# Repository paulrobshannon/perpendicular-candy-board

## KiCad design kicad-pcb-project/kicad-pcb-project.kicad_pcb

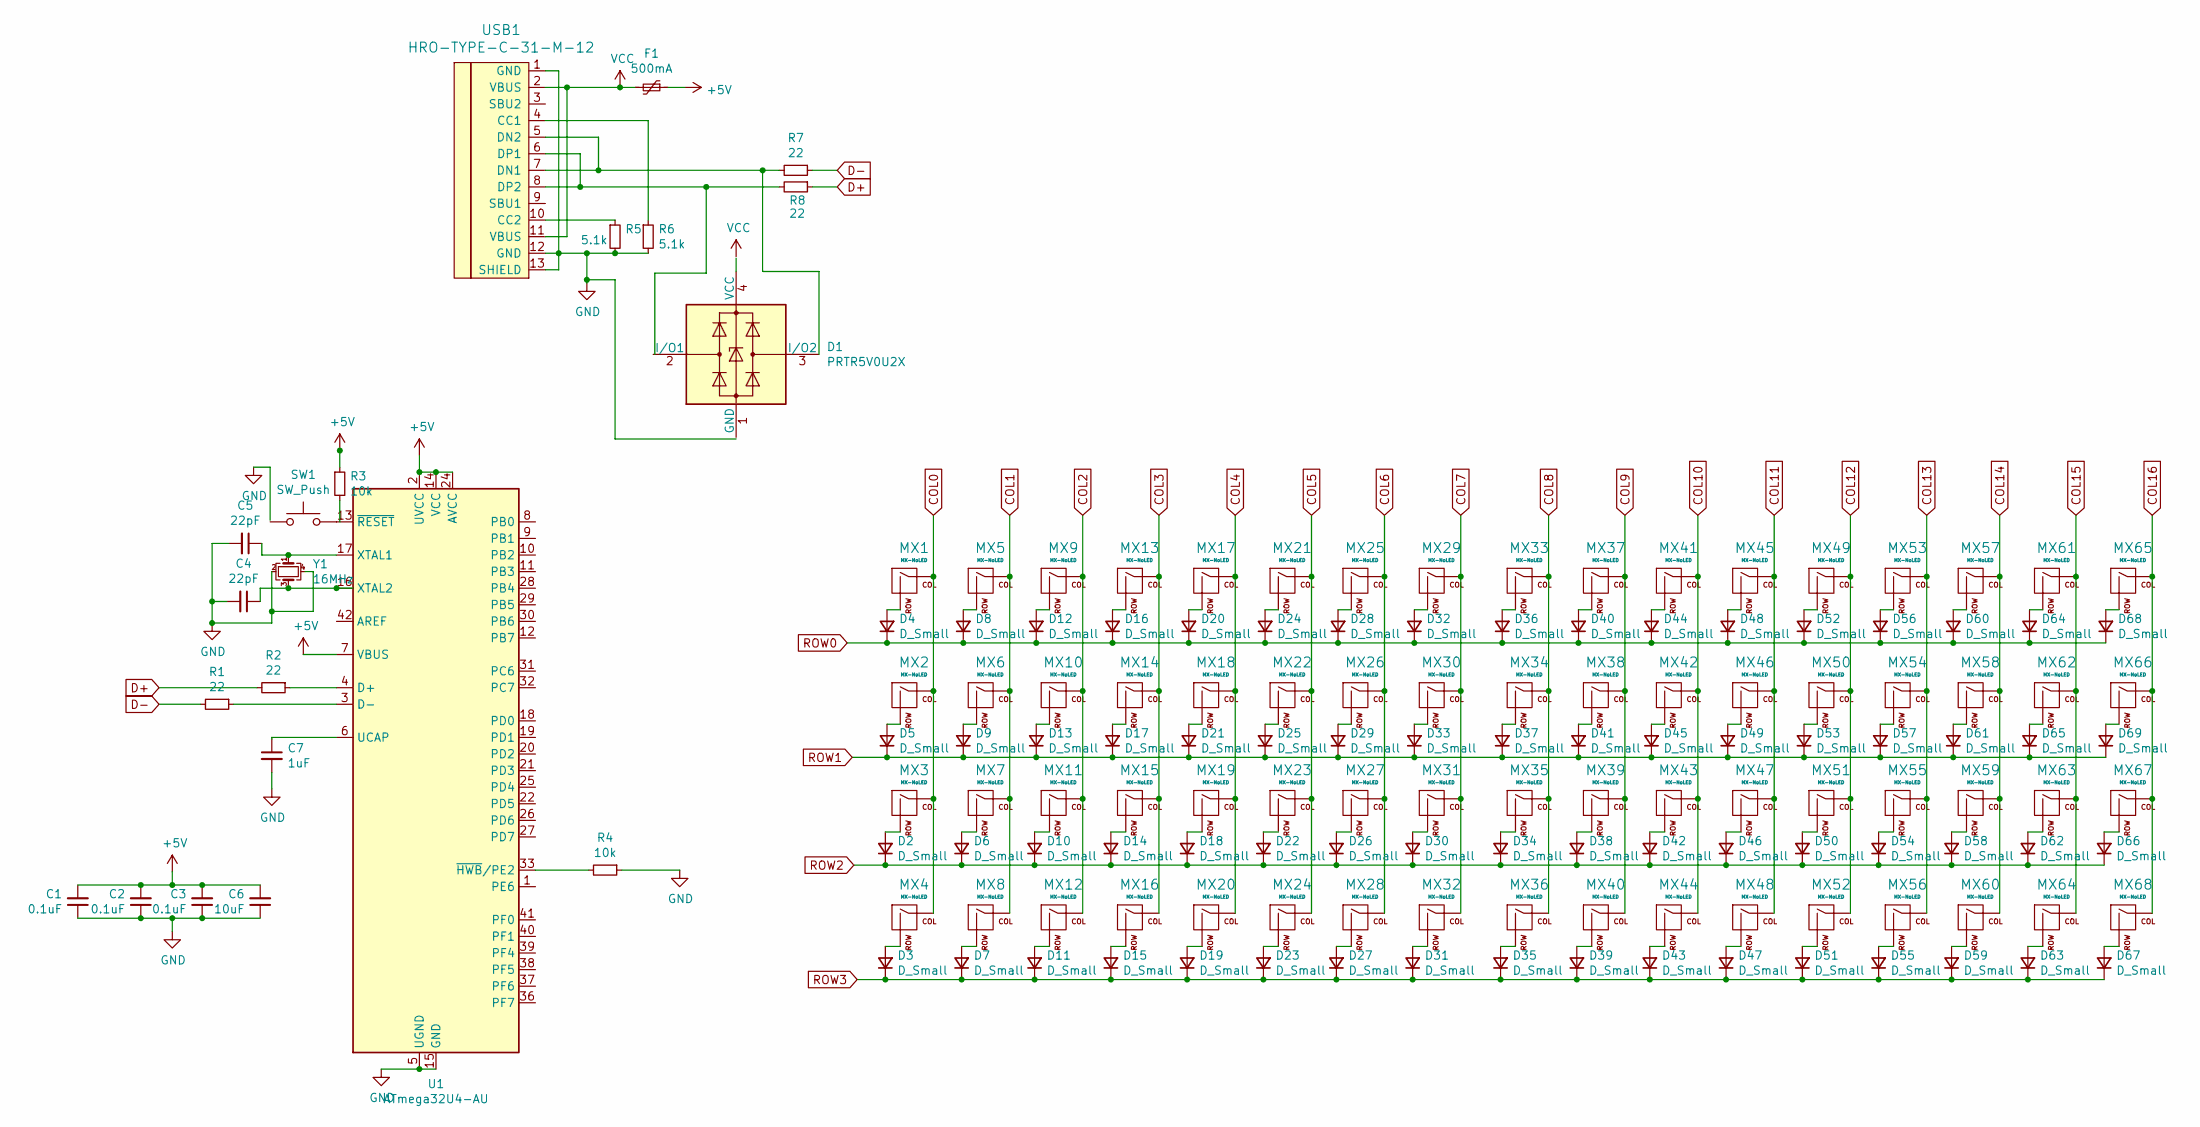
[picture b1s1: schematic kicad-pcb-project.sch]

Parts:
C1, C2, C3: 0.1uF; C_0805_2012Metric
C4, C5: 22pF; C_0805_2012Metric
C6: 10uF; C_0805_2012Metric
C7: 1uF; D_SOD-123
D1: PRTR5V0U2X; D_SOD-123
D2, D3, D4, D5, D6, D7, D8, D9, D10, D11, D12, D13, D14, D15, D16, D17, D18, D19, D20, D21, D22, D23, D24, D25, D26, D27, D28, D29, D30, D31, D32, D33, D34, D35, D36, D37, D38, D39, D40, D41, D42, D43, D44, D45, D46, D47, D48, D49, D50, D51, D52, D53, D54, D55, D56, D57, D58, D59, D60, D61, D62, D63, D64, D65, D66, D67, D68, D69: D_Small; D_SOD-123
F1: 500mA; Fuse_1206_3216Metric
MX1, MX2, MX3, MX4, MX5, MX6, MX7, MX8, MX9, MX10, MX11, MX12, MX13, MX14, MX15, MX16, MX17, MX18, MX19, MX20, MX21, MX22, MX23, MX24, MX25, MX26, MX27, MX28, MX29, MX30, MX31, MX32, MX33, MX34, MX35, MX36, MX37, MX38, MX39, MX40, MX41, MX42, MX43, MX44, MX45, MX46, MX47, MX48, MX49, MX50, MX51, MX52, MX53, MX54, MX55, MX56, MX57, MX58, MX59, MX60, MX61, MX62, MX63, MX64, MX65, MX66, MX67, MX68: MX-NoLED; Kailh_socket_MX
R1, R2, R7, R8: 22; R_0805_2012Metric
R3, R4: 10k; R_0805_2012Metric
R5, R6: 5.1k; R_0805_2012Metric
SW1: SW_Push; SKQG-1155865
U1: ATmega32U4-AU; TQFP-44_10x10mm_P0.8mm
USB1: HRO-TYPE-C-31-M-12; HRO-TYPE-C-31-M-12-Assembly
Y1: 16MHz; Crystal_SMD_3225-4Pin_3.2x2.5mm

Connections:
+5V: C1.2, C2.2, C3.2, C6.2, F1.1, R3.1, U1.2 (UVCC), U1.7 (VBUS), U1.14 (VCC), U1.24 (AVCC), U1.34 (VCC), U1.44 (AVCC)
COL0: MX1.1 (COL), MX2.1 (COL), MX3.1 (COL), MX4.1 (COL)
COL1: MX5.1 (COL), MX6.1 (COL), MX7.1 (COL), MX8.1 (COL)
COL2: MX9.1 (COL), MX10.1 (COL), MX11.1 (COL), MX12.1 (COL)
COL3: MX13.1 (COL), MX14.1 (COL), MX15.1 (COL), MX16.1 (COL)
COL4: MX17.1 (COL), MX18.1 (COL), MX19.1 (COL), MX20.1 (COL)
COL5: MX21.1 (COL), MX22.1 (COL), MX23.1 (COL), MX24.1 (COL)
COL6: MX25.1 (COL), MX26.1 (COL), MX27.1 (COL), MX28.1 (COL)
COL7: MX29.1 (COL), MX30.1 (COL), MX31.1 (COL), MX32.1 (COL)
COL8: MX33.1 (COL), MX34.1 (COL), MX35.1 (COL), MX36.1 (COL)
COL9: MX37.1 (COL), MX38.1 (COL), MX39.1 (COL), MX40.1 (COL)
COL10: MX41.1 (COL), MX42.1 (COL), MX43.1 (COL), MX44.1 (COL)
COL11: MX45.1 (COL), MX46.1 (COL), MX47.1 (COL), MX48.1 (COL)
COL12: MX49.1 (COL), MX50.1 (COL), MX51.1 (COL), MX52.1 (COL)
COL13: MX53.1 (COL), MX54.1 (COL), MX55.1 (COL), MX56.1 (COL)
COL14: MX57.1 (COL), MX58.1 (COL), MX59.1 (COL), MX60.1 (COL)
COL15: MX61.1 (COL), MX62.1 (COL), MX63.1 (COL), MX64.1 (COL)
COL16: MX65.1 (COL), MX66.1 (COL), MX67.1 (COL), MX68.1 (COL)
D+: R2.2, R8.1
D-: R1.2, R7.1
GND: C1.1, C2.1, C3.1, C4.2, C5.2, C6.1, C7.2, R4.1, R5.2, R6.2, U1.5 (UGND), U1.15 (GND), U1.23 (GND), U1.35 (GND), U1.43 (GND), USB1.1 (GND), USB1.12 (GND), USB1.13 (SHIELD), Y1.2, Y1.4
unnamed: C4.1, U1.16 (XTAL2), Y1.3
unnamed: C5.1, U1.17 (XTAL1), Y1.1
unnamed: C7.1, U1.6 (UCAP)
unnamed: D1.3 (I/O2), R7.2, USB1.5 (DN2), USB1.7 (DN1)
unnamed: D2.2 (A), MX3.2 (ROW)
unnamed: D3.2 (A), MX4.2 (ROW)
unnamed: D4.2 (A), MX1.2 (ROW)
unnamed: D5.2 (A), MX2.2 (ROW)
unnamed: D6.2 (A), MX7.2 (ROW)
unnamed: D7.2 (A), MX8.2 (ROW)
unnamed: D8.2 (A), MX5.2 (ROW)
unnamed: D9.2 (A), MX6.2 (ROW)
unnamed: D10.2 (A), MX11.2 (ROW)
unnamed: D11.2 (A), MX12.2 (ROW)
unnamed: D12.2 (A), MX9.2 (ROW)
unnamed: D13.2 (A), MX10.2 (ROW)
unnamed: D14.2 (A), MX15.2 (ROW)
unnamed: D15.2 (A), MX16.2 (ROW)
unnamed: D16.2 (A), MX13.2 (ROW)
unnamed: D17.2 (A), MX14.2 (ROW)
unnamed: D18.2 (A), MX19.2 (ROW)
unnamed: D19.2 (A), MX20.2 (ROW)
unnamed: D20.2 (A), MX17.2 (ROW)
unnamed: D21.2 (A), MX18.2 (ROW)
unnamed: D22.2 (A), MX23.2 (ROW)
unnamed: D23.2 (A), MX24.2 (ROW)
unnamed: D24.2 (A), MX21.2 (ROW)
unnamed: D25.2 (A), MX22.2 (ROW)
unnamed: D26.2 (A), MX27.2 (ROW)
unnamed: D27.2 (A), MX28.2 (ROW)
unnamed: D28.2 (A), MX25.2 (ROW)
unnamed: D29.2 (A), MX26.2 (ROW)
unnamed: D30.2 (A), MX31.2 (ROW)
unnamed: D31.2 (A), MX32.2 (ROW)
unnamed: D32.2 (A), MX29.2 (ROW)
unnamed: D33.2 (A), MX30.2 (ROW)
unnamed: D34.2 (A), MX35.2 (ROW)
unnamed: D35.2 (A), MX36.2 (ROW)
unnamed: D36.2 (A), MX33.2 (ROW)
unnamed: D37.2 (A), MX34.2 (ROW)
unnamed: D38.2 (A), MX39.2 (ROW)
unnamed: D39.2 (A), MX40.2 (ROW)
unnamed: D40.2 (A), MX37.2 (ROW)
unnamed: D41.2 (A), MX38.2 (ROW)
unnamed: D42.2 (A), MX43.2 (ROW)
unnamed: D43.2 (A), MX44.2 (ROW)
unnamed: D44.2 (A), MX41.2 (ROW)
unnamed: D45.2 (A), MX42.2 (ROW)
unnamed: D46.2 (A), MX47.2 (ROW)
unnamed: D47.2 (A), MX48.2 (ROW)
unnamed: D48.2 (A), MX45.2 (ROW)
unnamed: D49.2 (A), MX46.2 (ROW)
unnamed: D50.2 (A), MX51.2 (ROW)
unnamed: D51.2 (A), MX52.2 (ROW)
unnamed: D52.2 (A), MX49.2 (ROW)
unnamed: D53.2 (A), MX50.2 (ROW)
unnamed: D54.2 (A), MX55.2 (ROW)
unnamed: D55.2 (A), MX56.2 (ROW)
unnamed: D56.2 (A), MX53.2 (ROW)
unnamed: D57.2 (A), MX54.2 (ROW)
unnamed: D58.2 (A), MX59.2 (ROW)
unnamed: D59.2 (A), MX60.2 (ROW)
unnamed: D60.2 (A), MX57.2 (ROW)
unnamed: D61.2 (A), MX58.2 (ROW)
unnamed: D62.2 (A), MX63.2 (ROW)
unnamed: D63.2 (A), MX64.2 (ROW)
unnamed: D64.2 (A), MX61.2 (ROW)
unnamed: D65.2 (A), MX62.2 (ROW)
unnamed: D66.2 (A), MX67.2 (ROW)
unnamed: D67.2 (A), MX68.2 (ROW)
unnamed: D68.2 (A), MX65.2 (ROW)
unnamed: D69.2 (A), MX66.2 (ROW)
unnamed: R1.1, U1.3 (D-)
unnamed: R2.1, U1.4 (D+)
unnamed: R4.2, U1.33 (~HWB~/PE2)
unnamed: R5.1, USB1.10 (CC2)
unnamed: R6.1, USB1.4 (CC1)
unnamed: R8.2, USB1.6 (DP1), USB1.8 (DP2)
unnamed: SW1.2, U1.13 (~RESET)
ROW0: D4.1 (K), D8.1 (K), D12.1 (K), D16.1 (K), D20.1 (K), D24.1 (K), D28.1 (K), D32.1 (K), D36.1 (K), D40.1 (K), D44.1 (K), D48.1 (K), D52.1 (K), D56.1 (K), D60.1 (K), D64.1 (K), D68.1 (K)
ROW1: D5.1 (K), D9.1 (K), D13.1 (K), D17.1 (K), D21.1 (K), D25.1 (K), D29.1 (K), D33.1 (K), D37.1 (K), D41.1 (K), D45.1 (K), D49.1 (K), D53.1 (K), D57.1 (K), D61.1 (K), D65.1 (K), D69.1 (K)
ROW2: D2.1 (K), D6.1 (K), D10.1 (K), D14.1 (K), D18.1 (K), D22.1 (K), D26.1 (K), D30.1 (K), D34.1 (K), D38.1 (K), D42.1 (K), D46.1 (K), D50.1 (K), D54.1 (K), D58.1 (K), D62.1 (K), D66.1 (K)
ROW3: D3.1 (K), D7.1 (K), D11.1 (K), D15.1 (K), D19.1 (K), D23.1 (K), D27.1 (K), D31.1 (K), D35.1 (K), D39.1 (K), D43.1 (K), D47.1 (K), D51.1 (K), D55.1 (K), D59.1 (K), D63.1 (K), D67.1 (K)
VCC: F1.2, USB1.2 (VBUS), USB1.11 (VBUS)

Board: 2 copper layers, 157 parts (0 on the bottom side), 105 nets, no tracks yet.

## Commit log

2020-08-28 init commit
2020-08-28 added layout image
2020-08-29 adding kicad project and structure
2020-08-29 adding project libs
2020-09-03 switches added to schematic
2020-09-03 adding type-c submodules to project
2020-09-03 added usb-c to schematic
2020-09-03 adding resource url
2020-09-03 added footprints
2020-09-03 pcb grid arrange mx switches
2020-09-07 adding additional layouts to switch matrix
2020-09-07 adding pdf of schematic and .gitignore file
2020-09-15 updating schematic to include the soph68 by nicoles components ex-switch grid
